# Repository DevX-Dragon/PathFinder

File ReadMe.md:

# Path Finder
I made this PCB Fidget toy cause why not?. It helps me releive my stress as I suffer alot of school stress. It has keys and leds which powered by the xiao rp2040. It has multiple animations and stuff you could play with!.

## Layout

## BOM
|Product Name       |Quanity |Link                                                 |Price  |
|-------------------|--------|-----------------------------------------------------|-------|
|PCB                |1       |JLC PCB                                              |$4.00  |
|Seeed Studio RP2040|1       |[Aliexpress](https://www.aliexpress.com/item/1005011828090971.html)|$10.00 |
|JSTH 1x02 Connector|1       |[Aliexpress](https://www.aliexpress.com/item/1005004955655144.html)|$1.00  |
|LEDs               |3       |[Aliexpress](https://www.aliexpress.com/item/1005005708510866.html)|$1.00  |
|470 Resistor       |3       |[Aliexpress](https://www.aliexpress.com/item/1005002239656334.html)|$1.00  |
|MX Switches        |3       |[Aliexpress](https://www.aliexpress.com/item/4000538042437.html)   |$5.00  |
|DSA KeyCaps        |3       |[Aliexpress](https://www.aliexpress.com/item/32842379355.html)     |$5.00  |
|                   |        |                                                     |       |
|                   |**Shipping**|                                                     |$20.00 |
|                   |**Total**  |                                                     |**$47.00** |

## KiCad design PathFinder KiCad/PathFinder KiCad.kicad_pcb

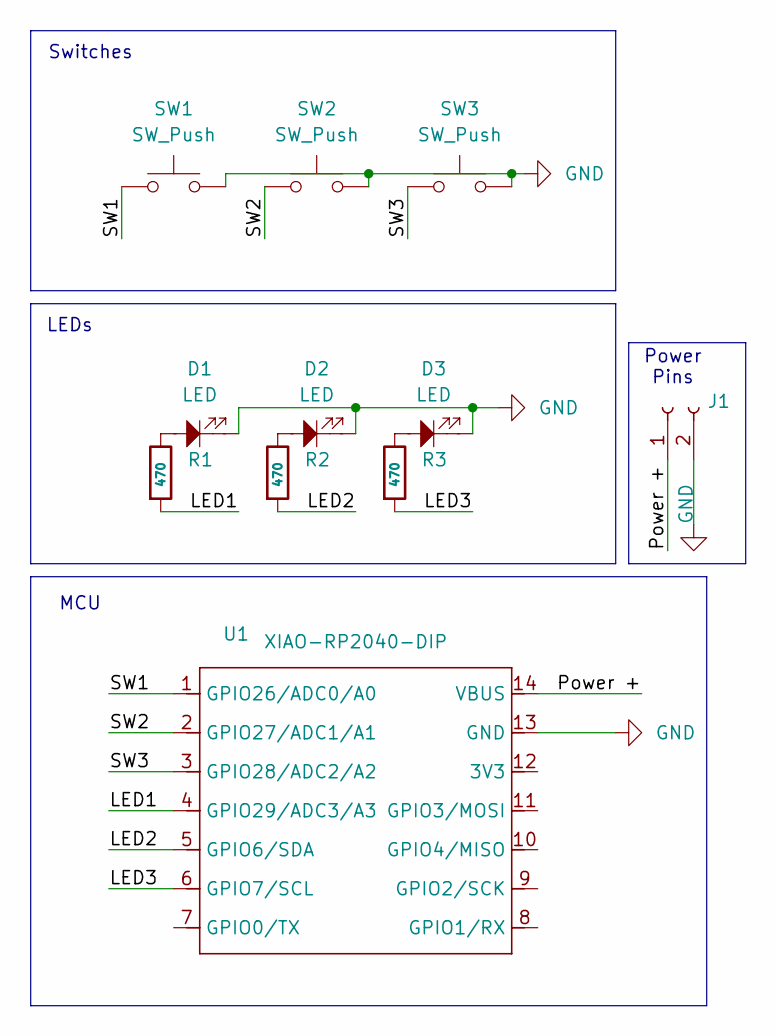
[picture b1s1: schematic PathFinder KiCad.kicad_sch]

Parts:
D1, D2, D3: LED; LED_D5.0mm
J1: Conn_01x02_Socket; Connector_1x02_JST-PH
R1, R2, R3: 470; R_Axial_DIN0204_L3.6mm_D1.6mm_P5.08mm_Horizontal
SW1, SW2, SW3: SW_Push; SW_Cherry_MX_1.00u_PCB
U1: XIAO-RP2040-DIP

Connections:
/LED1: R1.2, U1.4 (GPIO29/ADC3/A3)
/LED2: R2.2, U1.5 (GPIO6/SDA)
/LED3: R3.2, U1.6 (GPIO7/SCL)
/Power +: J1.1, U1.14 (VBUS)
/SW1: SW1.1, U1.1 (GPIO26/ADC0/A0)
/SW2: SW2.1, U1.2 (GPIO27/ADC1/A1)
/SW3: SW3.1, U1.3 (GPIO28/ADC2/A2)
GND: D1.1, D2.1, D3.1, J1.2, SW1.2, SW2.2, SW3.2, U1.13 (GND)
unnamed: D1.2, R1.1
unnamed: D2.2, R2.1
unnamed: D3.2, R3.1

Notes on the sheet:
LEDs
Power Pins
Switches
MCU

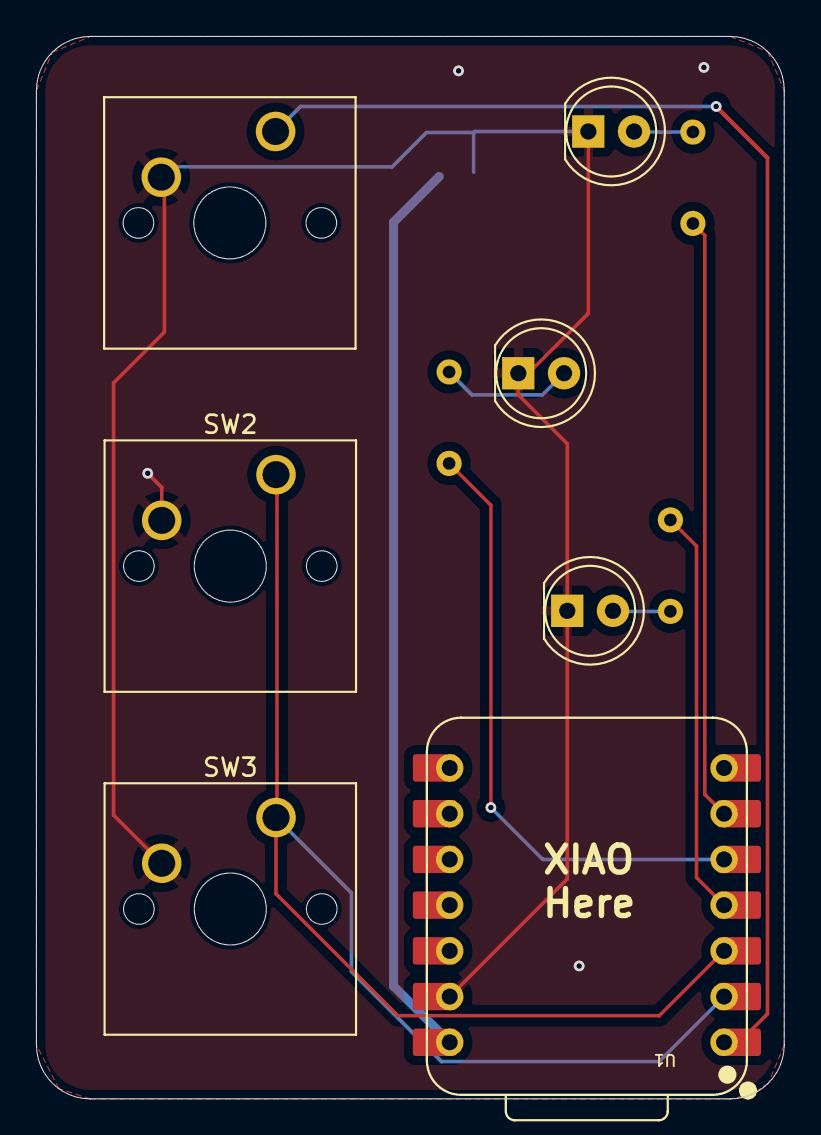
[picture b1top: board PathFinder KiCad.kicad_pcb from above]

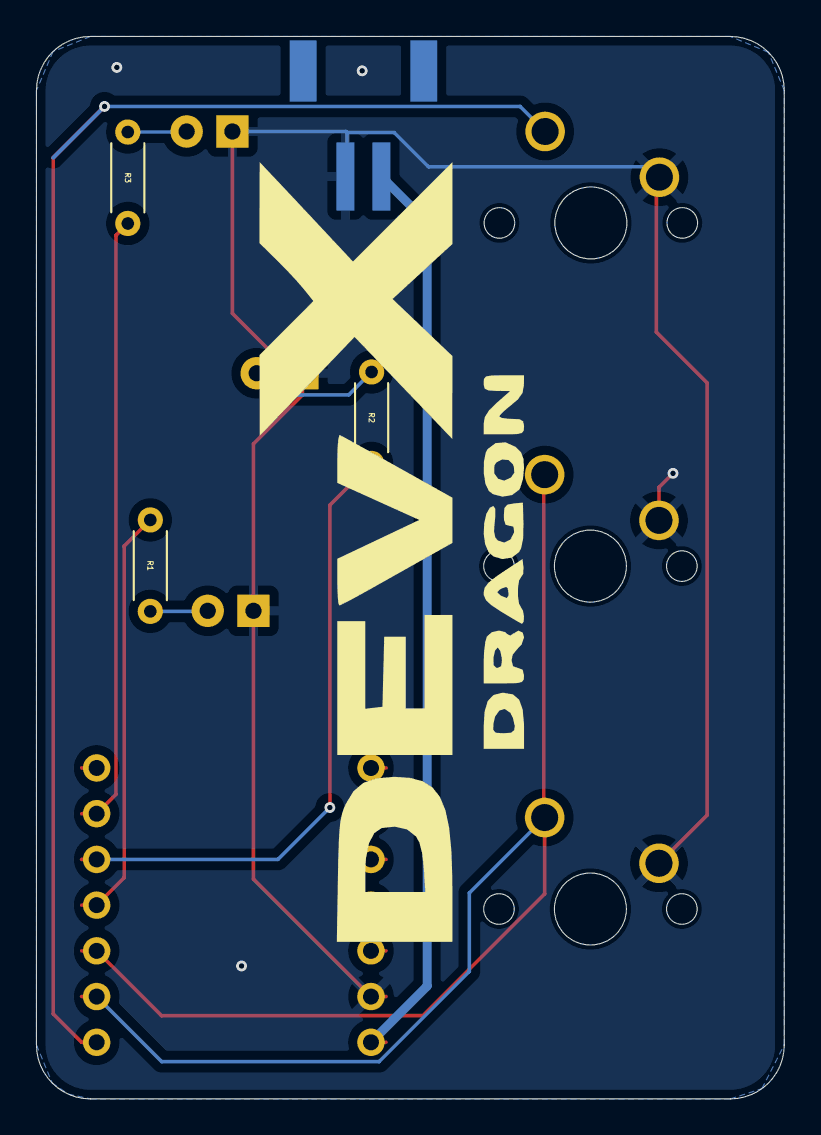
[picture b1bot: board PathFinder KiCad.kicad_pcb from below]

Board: 2 copper layers, 41.5 x 59.0 mm, 11 parts (4 on the bottom side), 11 nets.

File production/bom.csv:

Designator,Footprint,Quantity,Value,LCSC Part #
"D1, D2, D3",LED_D5.0mm,3,LED,
J1,Connector_1x02_JST-PH,1,Conn_01x02_Socket,C295747
"R1, R2, R3",R_Axial_DIN0204_L3.6mm_D1.6mm_P5.08mm_Horizontal,3,470,
"SW1, SW2, SW3",SW_Cherry_MX_1.00u_PCB,3,SW_Push,
U1,XIAO-RP2040-DIP,1,XIAO-RP2040-DIP,

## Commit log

2026-04-01 Initial
2026-04-01 Extra
2026-04-01 git prep 010426-1353
2026-04-01 readme
2026-04-01 Firmware
2026-04-05 KiCad Fix
